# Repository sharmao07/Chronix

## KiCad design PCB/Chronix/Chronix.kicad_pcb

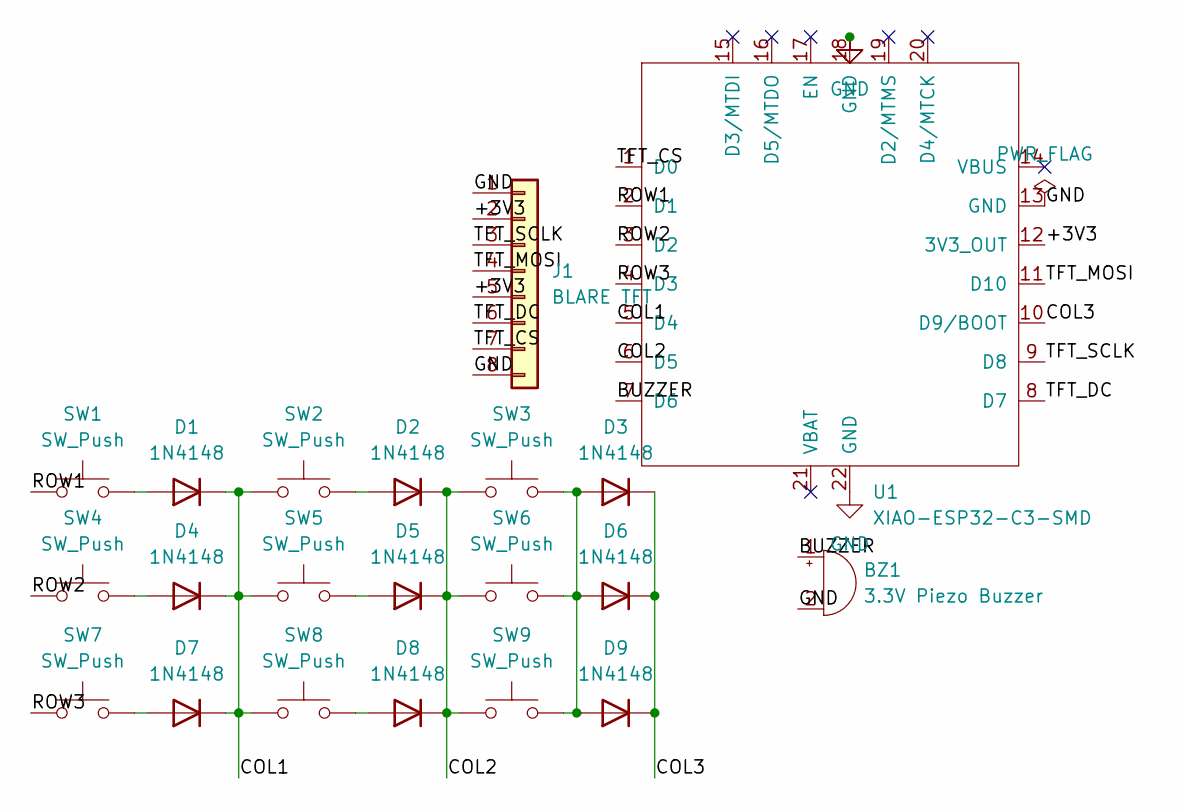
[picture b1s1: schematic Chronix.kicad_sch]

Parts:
BZ1: 3.3V Piezo Buzzer; Buzzer_12x9.5RM7.6
D1, D2, D3, D4, D5, D6, D7, D8, D9: 1N4148; D_DO-35_SOD27_P7.62mm_Horizontal
J1: BLARE TFT; PinHeader_1x08_P2.54mm_Vertical
SW1, SW2, SW3, SW4, SW5, SW6, SW7, SW8, SW9: SW_Push; SW_Cherry_MX_1.00u_PCB
U1: XIAO-ESP32-C3-SMD

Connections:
/+3V3: J1.2, J1.5, U1.12 (3V3_OUT)
/BUZZER: BZ1.1 (+), U1.7 (D6)
/COL1: D1.1 (K), D4.1 (K), D7.1 (K), SW2.1, SW5.1, SW8.1, U1.5 (D4)
/COL2: D2.1 (K), D5.1 (K), D8.1 (K), SW3.1, SW6.1, SW9.1, U1.6 (D5)
/COL3: D3.1 (K), D6.1 (K), D9.1 (K), U1.10 (D9/BOOT)
/ROW1: SW1.1, U1.2 (D1)
/ROW2: SW4.1, U1.3 (D2)
/ROW3: SW7.1, U1.4 (D3)
/TFT_CS: J1.7, U1.1 (D0)
/TFT_DC: J1.6, U1.8 (D7)
/TFT_MOSI: J1.4, U1.11 (D10)
/TFT_SCLK: J1.3, U1.9 (D8)
GND: BZ1.2 (-), J1.1, J1.8, U1.13 (GND), U1.18 (GND), U1.22 (GND)
unnamed: D1.2 (A), SW1.2
unnamed: D2.2 (A), SW2.2
unnamed: D3.2 (A), D6.2 (A), D9.2 (A), SW3.2, SW6.2, SW9.2
unnamed: D4.2 (A), SW4.2
unnamed: D5.2 (A), SW5.2
unnamed: D7.2 (A), SW7.2
unnamed: D8.2 (A), SW8.2

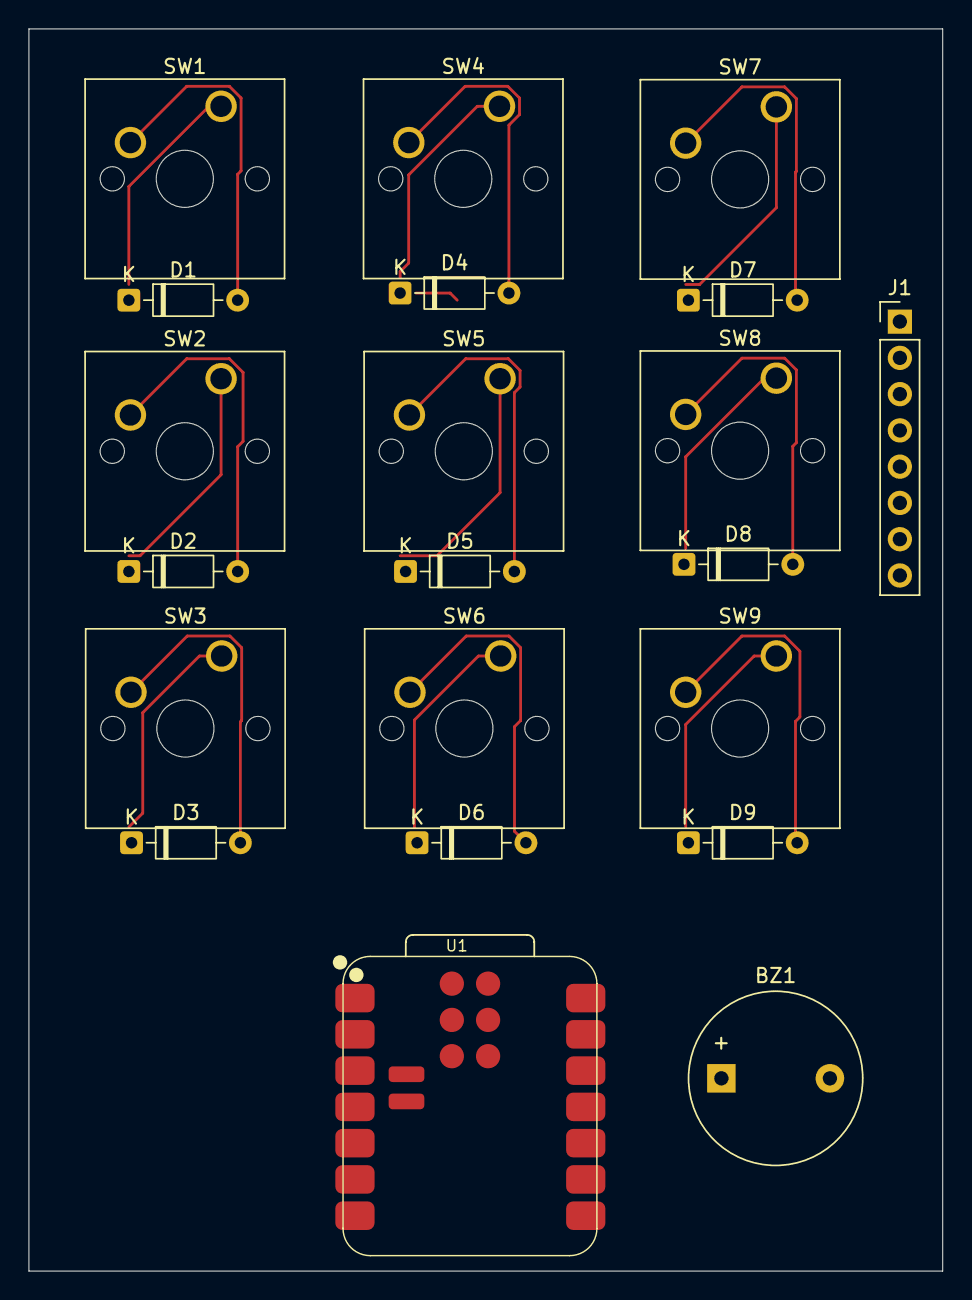
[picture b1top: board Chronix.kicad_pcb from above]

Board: 2 copper layers, 64.0 x 87.0 mm, 21 parts (0 on the bottom side), 20 nets.
